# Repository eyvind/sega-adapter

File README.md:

# Sega Mega Drive (Genesis) controller to Atari 8-bit adapter

Adapt a Sega Mega Drive controller to the 9-pin Atari joystick standard
using a Microchip PIC 16F1847 microcontroller.

![An 8BitDo M30 controller above an uncased circuit board populated with
an 18-pin chip, a capacitor, a male DE-9 socket, and an IDC-connected
ribbon cable terminated by a female DE-9 plug. An 8BitDo Retro receiver
is plugged in to the adapter](img/adapter.jpeg)

This adapter is compatible with [most
computers](#computer-compatibility) that use the Atari 9-pin joystick
connector, supporting most of the features of [Sega Mega Drive
controllers](#controller-compatibility), which use the same connector
with a slightly different pinout.  The Mega Drive was known as Genesis
in the US.

Read all you need to?  [Here's how to build the adapter](#build).

## Features of this adapter

The adapter uses a microcontroller to talk to the Mega Drive controller
and map its four buttons to the three inputs available on an 8-bit
Atari.

The B button on the controller is mapped to the normal joystick button.
Buttons A and C are connected to pins 5 and 9 on the joystick port;
these can be read as extra joystick buttons by the computer.  Most games
that only support one extra button use the C button (pin 9).

### "A is Up" toggle

The start button has no natural mapping since the Atari can only read
three buttons, but a common complaint in platform games on the Atari
(and later the Amiga) was that they often used joystick Up to jump
because of the lack of extra joystick buttons.

A dedicated Up button would solve this problem, but the Start button is
not usually in a good location to be used as a jump button.  The adapter
therefore supports this feature indirectly: holding the Start button
down for a second maps the A button to Up.

Since the joystick button often starts games, a short press of the Start
button is mapped to joystick button 1.  This allows Start to both serve
its normal function (in supported games) and switch the A button between
modes.

### SNACK enhanced mode

[SNACK](https://abbuc.de/produkt/snack-adapter/) is an Atari adapter for
SNES controllers.  It has an enhanced mode that allows all of the
buttons to be read by the Atari, and this adapter supports that mode if
you have a six-button controller.

To switch to SNACK mode on a Sega controller, press Mode, Start, and C
(the right shoulder button if you're using an 8BitDo M30 controller) at
the same time.  Mode+Start+Z (left shoulder on the M30) goes back to
normal mode.

If you're using an 8BitDo Retro Receiver with an Xbox or PlayStation
controller, the button layout is different.  Press Mode+Start+X (left
shoulder) to switch to SNACK mode on these controllers, and Mode+Start+Z
(right shoulder) to go back to normal mode.

The SNES controller has four main buttons: A, B, X, and Y; left and
right shoulder buttons; and START and SELECT.

The main buttons have the same labels and approximately the same diamond
configuration as the A, B, X, and Y buttons on a Mega Drive controller,
but the AB and XY buttons are swapped.

The Mega Drive controller does not have shoulder buttons, so the Z and C
buttons are used instead.  As noted above, the 8BitDo Retro Receiver
maps Z and C to the shoulder buttons on the M30 controller.

Finally, the Mode button stands in for SELECT.

#### Notes

- SNACK mode uses the joystick ports in a completely different way to a
  normal joystick and will produce unexpected results in software that
  is not written to detect it.
- The buttons are not completely independent.  Only one of START, SELECT
  (Mode), X, and Y can be detected at any time, and any of those buttons
  will override A and B.  However, A and B are independent of each
  other, and the shoulder buttons are entirely independent.
- Centering the joystick relies on fairly precise timing to charge the
  Atari's pot capacitors to a specific range, so different computers and
  even cable lengths may make the joystick appear to be intermittently
  leaning in one direction.
- This feature is still experimental.

### Autodetection (Atari 8-bit machines only)

Because of the way the paddle circuits are used to read the second and
third button inputs, 8-bit Ataris read an unconnected second or third
button input as if the button is being held down.

This allows\* games running on the computer to detect the presence of a
multibutton controller by assuming that a button does not exist until it
has been seen to be released.  The adapter supports this autodetection
by leaving its button outputs open unless a Mega Drive controller is
detected or the corresponding button input is pulled low.

To activate the second button when a Mega Drive controller is not
connected, pin 9 on the controller input must be pulled low before the
adapter starts driving the second button output.  This means that the
second button must be pressed once before it can be detected by the
computer.

The third button output is open unless a Mega Drive controller is
detected since there is no other source for a third button input.

\* The astute reader will note that games are _required_ to ignore
button inputs until the button is released, otherwise a nonexistent
button will appear to be continually held down.

## Computer compatibility
### 8-bit Atari computers

The adapter has mostly been tested on 8-bit Ataris using
[Joy2B+](https://github.com/ascrnet/Joy2Bplus) enhanced games.

### 8-bit Commodore computers

The C64, C128, and VIC-20 can also read the second and third buttons.
The extra buttons on these machines are active high, which is opposite
to Atari and Sega.

Pulling the /C64 pin (number 4) on the PIC low inverts the outputs for
the extra buttons, allowing them to be read correctly by the 8-bit
Commodores.  The simplest way to do this is to install a jumper in the
appropriate location on the circuit board.

Because the joystick inputs of the 8-bit Commodores are somewhat
sensitive, all of the pins are normally open (floating).  The extra
button pins are pulled high when active, all other signals are pulled
low when active.

### Amiga

Unlike the 8-bit Commodores the extra buttons on the Amiga are active
low, and unlike all the 8-bit computers they are digital inputs instead
of repurposed paddle circuits.  The Atari mode supports both Atari and
Amiga by driving the pins for buttons two and three both high and low.

### Atari ST (untested)

Button two registers as the second mouse button / port 1 joystick button
if the adapter is plugged into port 0.  The ST does not support
additional joystick buttons on port 1.

## Controller compatibility
### Sega controllers

The adapter is compatible with three- and six-button Mega Drive
controllers. On six-button controllers, buttons X, Y, and Z act as
autofire versions of A, B, and C, while the Mode button is only used for
[SNACK enhanced mode](#snack-enhanced-mode).

Sega Master System controllers are theoretically supported, including
the second button, but this is untested.

### 8BitDo Retro Receiver

The adapter is extensively tested with the [8BitDo Retro Receiver for
SEGA](https://www.8bitdo.com/retro-receiver-genesis-mega-drive/).  It's
a nifty way to use wireless controllers on old hardware.

### Other joysticks or controllers

A controller or joystick with a second button that is not normally
recognised by 8-bit Atari and Commodore computers _may_ work through the
adapter.

**CAUTION:** the second button must be on pin 9 and _not_ pin 5.  Pin 5
is the power pin, and pulling it low may damage your computer or the
adapter.

Single-button joysticks will work but derive no benefit from using the
adapter.

### Atari 7800 controller, Commodore multi-button joysticks, paddles, steering wheels, etc.

These devices will not work and should not be plugged in to the adapter.

## Build

The schematics and parts list for the adapter are in the [kicad
directory](kicad).  If you don't already have a preferred way to
manufacture a PCB, you can order a set of three from [OSH
Park](https://oshpark.com/shared_projects/Nn84QTsl).  You also need a
way to [program the microcontroller](#program).

## Program

[JOY-2-PIC](https://ataribits.weebly.com/joy2pic.html) can program a PIC
using an Atari 8-bit computer's joystick port.  Boot from the .atr image
attached to each release to start programming.  If you have a USB PIC
programmer connected to a PC, use the .hex file instead.

## Modify

If you want to modify the firmware, you need the [xc8
compiler](https://www.microchipdeveloper.com/xc8:installation) from
Microchip to build it.  Run `rake` or `xc8-cc -mcpu=16f1847 -o
sega-adapter.hex *.c` to create a .hex file suitable for a PIC
programmer.

## Rationale

All right, it's time for some history.

- In 1977, Atari released the 2600 game console.
- In 1981, Commodore released the VIC-20 home computer.
- In 1984, Sega released the SG-1000 II console with one main
  improvement from the SG-1000: detachable controllers.

These machines all used the same physical connector with an almost
identical pinout for their controllers, and their manufacturers stuck
with the standard through later generations, tempting people to swap
controllers and joysticks between the systems.

Most of the time, this more or less worked.  Buttons were not always
completely compatible, but most Atari and Commodore games only supported
one button so it didn't really matter as long as one button worked.  One
important caveat: Sega chose to put power on pin 5 instead of pin 7, so
mixing and matching had the potential to cause damage to both machines
and controllers.

Initially each signal was carried by an individual pin: four pins for
directions, one for the button, two pins reserved for power and ground,
leaving two pins free for other functions.

### Mega Drive (Genesis)

For the Mega Drive, released in 1988, Sega wanted to have more buttons
(four) than there were available pins on the controller port (three).
They solved this problem by using one pin (7) as an output from the
console to the controller, allowing two pins (6 and 9) to multiplex the
A, B, C, and Start buttons.

### Joy2B+

Fast forward 20 years, to January 2019.  A poster on an [Atari 8-bit
forum](https://atariage.com/forums/topic/278884-2-button-joystick/?do=findComment&comment=4206381)
introduced a design for a three-button joystick for the 8-bit Ataris,
and -- crucially -- included patched versions of existing games that
supported the extra buttons.  This was the
[Joy2B+](https://github.com/ascrnet/Joy2Bplus) project.

Suddenly, there was a reason to connect a joystick with more than one
button to an Atari.

### 8BitDo Retro Receiver for SEGA

Finally, a month later, a Hong Kong-based company called 8BitDo released
a device that allowed Bluetooth game controllers to be used with Sega
consoles, the [8BitDo Retro Receiver for
SEGA](https://www.8bitdo.com/retro-receiver-genesis-mega-drive/)...
tantalisingly close to being compatible with Atari joystick ports.

## Pinout

```
                      PIC 16F1847
                     +---------_---------+
                     |                   |
            Atari 5 -|  1  RA2   RA1  18 |- Atari 1
                     |                   |
            Atari 6 -|  2  RA3   RA0  17 |- Atari 2
                     |                   |
            Atari 9 -|  3  RA4   RA7  16 |- Atari 3
                ___  |                   |
                C64 -|  4  RA5   RA6  15 |- Atari 4
                     |                   |
    Atari 8  SEGA 8 -|  5  GND   +5v  14 |- Atari 7  SEGA 5
                     |                   |
             SEGA 1 -|  6  RB0   RB7  13 |- SEGA 6
                     |                   |
             SEGA 2 -|  7  RB1   RB6  12 |- SEGA 7
                     |                   |
             SEGA 3 -|  8  RB2   RB5  11 |- SEGA 9
                     |                   |
             SEGA 4 -|  9  RB3   RB4  10 |- X
                     |                   |
                     +-------------------+
```

## Acknowledgements

Information on reading Sega controllers came from
https://github.com/jonthysell/SegaController/wiki/How-To-Read-Sega-Controllers
and
https://www.raspberryfield.life/2019/03/25/sega-mega-drive-genesis-6-button-xyz-controller/

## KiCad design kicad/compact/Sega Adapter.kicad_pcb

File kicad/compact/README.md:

# Compact adapter

The compact variant of the adapter is the recommended one to build.
DigiKey part numbers are provided as a convenience, but alternative
parts can certainly be used.

## BOM

| Component | DigiKey part number |
| --- | --- |
| PIC 16F1874 microcontroller | PIC16F1847-I/P-ND |
| 0.1uF capacitor | 1109PHCT-ND |
| 18-pin socket | ED3018-ND |
| D-sub male socket | A32088-ND |
| IDC header | S2011EC-05-ND |
| D-sub female plug with ribbon cable | H7FXH-0906G-ND |
| IDC connector | LKR10H-ND |
| Jumper header (optional) | S2011EC-01-ND |
| Jumper (optional) | S9001-ND |

### Optional jumper

The jumper is used to switch the adapter between Atari and C64 mode.  If
the adapter is only going to be used with one kind of computer, the
jumper and its header can either be omitted entirely (Atari/Amiga) or
replaced with a solder bridge or wire (C64/VIC-20).

### Optional joystick pigtail

Instead of using the IDC header and ribbon cable, a joystick pigtail can
be soldered directly to the board.  A cable from an old joystick or one
end of a joystick extension cable can be used for a pigtail; just make
sure that it has nine wires.

## Assembly notes

- The ribbon cable is 2m long, so it is a good idea to cut it to a more
  reasonable length.  The remaining cable can be used with standalone
  d-sub connectors (part number HHFP09H-ND) to make more adapters.

- When attaching the IDC connector to the ribbon cable, make sure that
  pin 1 (the red wire) is flush against the side and that there is a
  small gap on the other side.  This is because the connector has ten
  pins while the cable only has nine.

- Make sure that pin 1 of the cable is on the same side as pin 1 of the
  header when connecting the cable to the board.  Pin 1 is the one with
  the square pad on the circuit board.

- If you are using alternative parts, please note that there isn't much
  clearance between the IC socket and the IDC header.  Depending on the
  socket used, a shrouded IDC header may not fit.

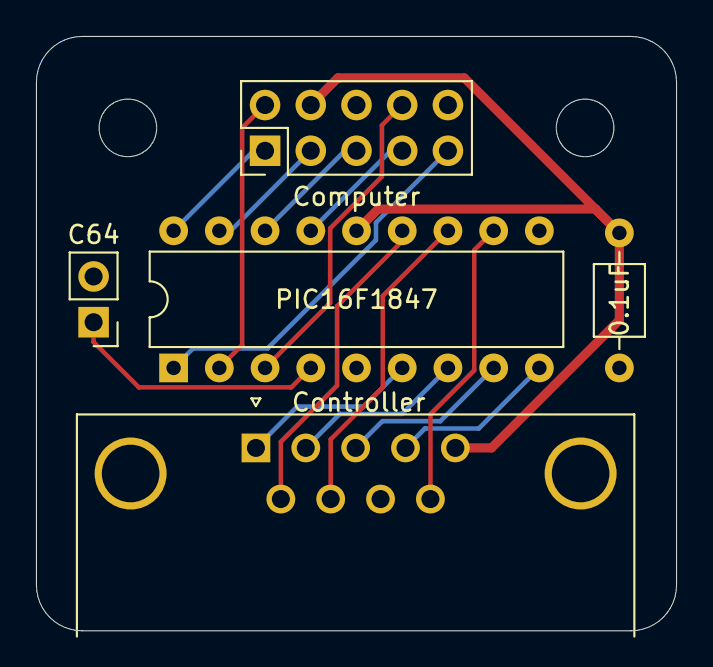
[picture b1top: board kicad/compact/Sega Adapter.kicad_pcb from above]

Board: 2 copper layers, 35.6 x 33.0 mm, 5 parts (0 on the bottom side), 17 nets.

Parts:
C1: 0.1uF; C_Axial_L3.8mm_D2.6mm_P7.50mm_Horizontal
J1: Controller; DSUB-9_Male_Horizontal_P2.77x2.84mm_EdgePinOffset7.70mm_Hou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
J2: Computer; PinHeader_2x05_P2.54mm_Vertical
JP1: C64; PinHeader_1x02_P2.54mm_Vertical
U1: PIC16F1847; DIP-18_W7.62mm

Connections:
+5V: C1.2, J1.5, J2.4, U1.14
GND: C1.1, J1.0, J1.8, J2.6, JP1.2, U1.5
unnamed: J1.1, U1.6
unnamed: J1.2, U1.7
unnamed: J1.3, U1.8
unnamed: J1.4, U1.9
unnamed: J1.6, U1.13
unnamed: J1.7, U1.12
unnamed: J1.9, U1.11
unnamed: J2.1, U1.18
unnamed: J2.2, U1.2
unnamed: J2.3, U1.17
unnamed: J2.5, U1.16
unnamed: J2.7, U1.15
unnamed: J2.8, U1.3
unnamed: J2.9, U1.1
unnamed: JP1.1, U1.4

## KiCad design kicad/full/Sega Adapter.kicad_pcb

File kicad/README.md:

# KiCad schematic

This PCB features a detachable ribbon cable to connect it to the
computer and an optional jumper to switch the adapter to C64 mode.

PCBs can be ordered in sets of three from [OSH
Park](https://oshpark.com/shared_projects/Nn84QTsl), or any other PCB
manufacturer that accepts KiCad schematics.

The previously available alternative versions of the PCB have been
removed for simplicity.  They can still be found in git history.

DigiKey part numbers are provided as a convenience but alternative
parts can certainly be used.

## BOM

| Component | DigiKey part number |
| --- | --- |
| PIC 16F1874 microcontroller | PIC16F1847-I/P-ND |
| 0.1uF capacitor | 1109PHCT-ND |
| 18-pin socket | ED3018-ND |
| D-sub male socket | A32088-ND |
| IDC header | S2011EC-05-ND |
| D-sub female plug with ribbon cable | H7FXH-0906G-ND |
| IDC connector | LKR10H-ND |
| Jumper header (optional) | S2011EC-01-ND |
| Jumper (optional) | S9001-ND |

### Optional jumper

The jumper is used to switch the adapter between Atari and C64 mode.  If
the adapter is only going to be used with one kind of computer, the
jumper and its header can either be omitted entirely (Atari/Amiga) or
replaced with a solder bridge or wire (C64/VIC-20).

### Optional joystick pigtail

Instead of using the IDC header and ribbon cable, a joystick pigtail can
be soldered directly to the board.  Any cable from an old joystick or
half of a joystick extension cable can be used for a pigtail, as long as
it has nine wires.

## Assembly notes

- The ribbon cable is 2m long, so it is a good idea to cut it to a more
  reasonable length.  The remaining cable can be used with standalone
  d-sub connectors (part number HHFP09H-ND) to make more adapters.

- When attaching the IDC connector to the ribbon cable, make sure that
  pin 1 is flush against the side and that there is a small gap on the
  other side.  This is because the connector has ten pins while the
  cable only has nine.

- Make sure that pin 1 of the cable is on the same side as pin 1 of the
  header when connecting the cable to the board.  Pin 1 is the one with
  the square pad on the circuit board.

- If you are using alternative parts, please note that there isn't much
  clearance between the IC socket and the IDC header.  Depending on the
  socket used, a shrouded IDC header may not fit.

## Licence

The schematics for this project are licensed under the [Creative Commons
Attribution 4.0
International](https://creativecommons.org/licenses/by/4.0/) licence.
See [LICENSE](LICENSE) for details.

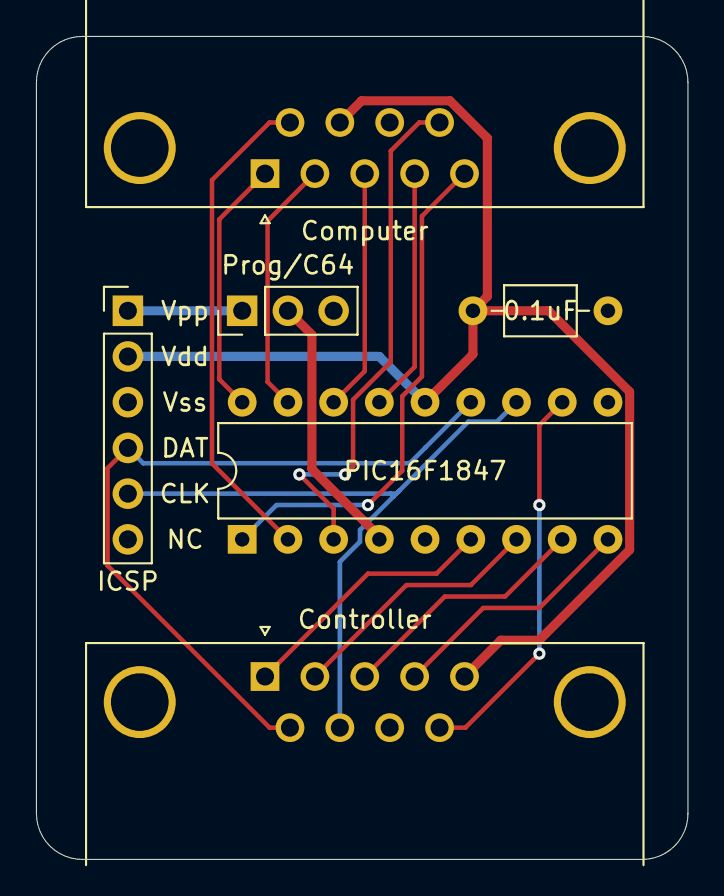
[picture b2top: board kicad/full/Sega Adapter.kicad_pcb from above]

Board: 2 copper layers, 36.2 x 45.7 mm, 6 parts (0 on the bottom side), 18 nets.

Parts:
C1: 0.1uF; C_Axial_L3.8mm_D2.6mm_P7.50mm_Horizontal
J1: Controller; DSUB-9_Male_Horizontal_P2.77x2.84mm_EdgePinOffset7.70mm_Hou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
J2: Computer; DSUB-9_Female_Horizontal_P2.77x2.84mm_EdgePinOffset7.70mm_H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
J3: ICSP; PinHeader_1x06_P2.54mm_Vertical
JP1: Prog/C64; PinHeader_1x03_P2.54mm_Vertical
U1: PIC16F1847; DIP-18_W7.62mm

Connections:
+5V: C1.2, J1.5, J2.7, J3.2, U1.14
GND: C1.1, J1.0, J1.8, J2.0, J2.8, J3.3, JP1.3, U1.5
unnamed: J1.1, U1.6
unnamed: J1.2, U1.7
unnamed: J1.3, U1.8
unnamed: J1.4, U1.9
unnamed: J1.6, J3.4, U1.13
unnamed: J1.7, J3.5, U1.12
unnamed: J1.9, U1.11
unnamed: J2.1, U1.18
unnamed: J2.2, U1.17
unnamed: J2.3, U1.16
unnamed: J2.4, U1.15
unnamed: J2.5, U1.1
unnamed: J2.6, U1.2
unnamed: J2.9, U1.3
unnamed: J3.1, JP1.1
unnamed: JP1.2, U1.4

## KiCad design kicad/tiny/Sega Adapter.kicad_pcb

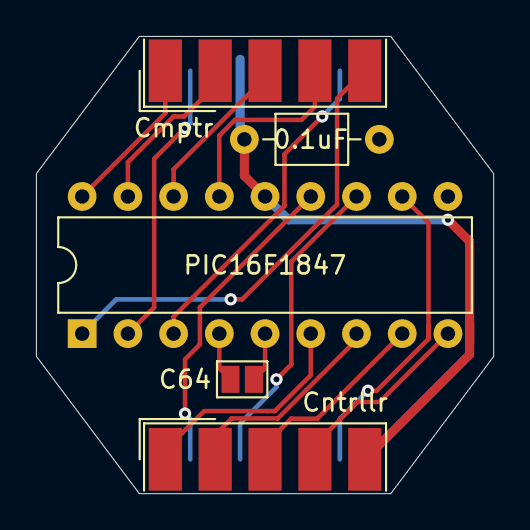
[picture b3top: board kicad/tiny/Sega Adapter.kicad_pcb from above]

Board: 2 copper layers, 25.4 x 25.4 mm, 5 parts (0 on the bottom side), 17 nets.

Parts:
C1: 0.1uF; C_Axial_L3.8mm_D2.6mm_P7.50mm_Horizontal
Cmptr: Atari; DSUB-9_Female_EdgeMount_P2.77mm
Cntrllr: Sega; DSUB-9_Male_EdgeMount_P2.77mm
JP1: C64; SolderJumper-2_P1.3mm_Open_Pad1.0x1.5mm
U1: PIC16F1847; DIP-18_W7.62mm

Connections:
+5V: C1.2, Cmptr.7, Cntrllr.5, U1.14
GND: C1.1, Cmptr.8, Cntrllr.8, JP1.2, U1.5
unnamed: Cntrllr.1, U1.6
unnamed: Cntrllr.2, U1.7
unnamed: Cntrllr.3, U1.8
unnamed: Cntrllr.4, U1.9
unnamed: Cntrllr.6, U1.13
unnamed: Cntrllr.7, U1.12
unnamed: Cntrllr.9, U1.11
unnamed: Cmptr.1, U1.18
unnamed: Cmptr.2, U1.17
unnamed: Cmptr.3, U1.16
unnamed: Cmptr.4, U1.15
unnamed: Cmptr.5, U1.1
unnamed: Cmptr.6, U1.2
unnamed: Cmptr.9, U1.3
unnamed: JP1.1, U1.4

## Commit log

2021-01-21 Correct spelling and add credit where due
    It's "Mega Drive" not "Megadrive." Apparently.
2021-01-21 Add 8-bit Commodore mode
    The second and third joystick buttons are used differently on the 8-bit
    Commodore computers; the potentiometer pins are pulled high instead of
    low when the button is pressed. Add an option to use the adapter with
    these machines.
2021-01-24 Move pins around to put outputs on PORTA
    The high-impedance input mode of the PORTB pins has insufficiently high
    impedance to use as a "low" state for buttons 2 and 3. Shift the pins
    around so that all outputs are on PORTA, where the input mode resistance
    is higher.
    Driving the pins high (for up/down/left/right/fire) or low (for buttons
    two and three) can cause problems for the 8-bit Commodores. Switching
2021-01-24 Simplify button state logic
    Make a new flag called TWO_BUTTON in the controller state to track if a
    second button is present, simplifying the code that disconnects the
    buttons in Atari mode and allowing it to use the same tristate logic as
    the Commodores.
    Remove the SIX_BUTTON flags since they're not used.
2021-01-24 Only write to TRISA once per scan
    Every write to a tristate register causes a read/modify/write cycle.
    Make a temporary variable for building the desired state, then write it
    to the register in one operation.
2021-03-07 Add Amiga support, programming info, and a wall of text
2021-04-25 Add KiCad files for pcb
2021-04-25 Add KiCad projects for two adapter variants
    The full adapter has an ICSP header for programming the PIC, a three-pin
    jumper for C64/programming mode, and through-hole D-sub connectors.
    The compact pcb removes the ICSP header but still has through-hole
    connectors and a jumper for C64 mode.
    The tiny pcb uses solder cup D-sub connectors and has a simple solder
    bridge jumper for C64 mode.
2021-05-09 Get rid of vias
2021-07-06 Switch compact adapter to IDC connector
2021-07-07 Add README and licence
    Also tweak the PCBs:
    - round the corners of the full PCB
    - add a copyright message to the full and tiny PCBs
2021-08-14 Hide the J2 label
2021-08-21 Add BOM and recommend the compact pcb
2021-08-21 Link to the schematics from the project README
2021-08-29 Add six-button support with autofire
    The select line toggle sequence to read the X, Y, Z, and MODE buttons is
    timing sensitive, and is too slow for the 8bitdo receiver with the PIC
    system clock at 500kHz (the default) or 1MHz. At 2MHz, it works.
    Without multiplexing on the computer side there's no way to use the
    extra buttons directly, but autofire is useful. Holding down X, Y, or Z
    respectively pulses the A, B, or C button at around 12Hz.
2022-08-13 Improve six-button compatibility
    Using a non-8bitdo test controller, 2MHz wasn't fast enough to enable
    six-button support. Go all the way to 32MHz (the highest clock speed on
    the 16F1847) to make it work.
2022-08-13 Save power by slowing the clock when idle
    The 32MHz clock requires 4xPLL to be enabled, but switching clocks
    resulted in the top clock speed alternating between 32MHz and 8MHz each
    cycle.
    16MHz seems to be fast enough to satisfy the test controller and does
    not require the 4xPLL.
2022-08-13 Adjust autofire
    Tune the autofire rate to match the 8BitDo adapter's native autofire,
    which is just over 16Hz. Pre-tuning, the rate was around 13Hz.
2022-08-13 Add six-button support to the README file
2022-08-13 Clarify the README a bit
2022-08-15 Add credit for six-button controller timings
2022-09-17 Add experimental SNACK support
    Hold down the MODE button to switch to SNACK mode.
    SNACK is a project that brings SNES controllers to Atari, and it has a
    "quite clever ;) but also easy to use" mapping for all SNES buttons to
    the Atari.
    The button layout is adapted to the SEGA controller thusly:
    - A and B are swapped
2022-09-19 Use SNACK buttons to switch modes
    SNACK uses START+SELECT+left/right shoulder buttons to switch between
    its classic and enhanced modes: when pressed in combination with START
    and SELECT, the right shoulder button switches to enhanced mode and the
    left goes back to classic mode.
    Since SNACK-compatible games may reference this convention, it makes
    sense to use it here.
2022-09-19 Don't toggle A-is-Up in SNACK mode
    The START key is directly useable when the controller is in SNACK mode,
    and A-is-Up is not. Don't hijack the START button when in SNACK mode.
2022-09-23 Run the SNACK cycle more often to smooth timing
    Charging the pot capacitors partway is very timing sensitive. Remove
    conditionals from the code and run a shorter charge twice as often to
    make it less jittery.
2022-09-24 Document SNACK enhanced mode
2022-12-04 Build with xc8-cc
    Building with xc8-cc instead of the older xc8 reveals some type
    warnings. Clean them up, and update the documentation and .gitignore
    for the new compiler.
2022-12-04 Refactor into more manageable source files
    Split sega-adapter.c into separate source files and add a Rakefile to
    make building easier.
2023-01-07 Add a picture of the compact adapter
2023-01-28 Add Snack support for Xbox/Playstation controllers
    The 8bitdo retro adapter's layout for Xbox/Playstation-style controllers
    needs a different Snack mapping than the Megadrive controller.
    Since the Snack adapter itself uses select/start/shoulder buttons to
    switch between enhanced and normal mode, it makes sense to use the same
    convention for this adapter:
    Start+select+
2023-01-29 Update README.md for the new SNACK mode
    The README also needed a rewrite, so give it one.
2023-01-30 Remove the full and tiny pcb variants

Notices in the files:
kicad/compact/Sega Adapter.kicad_pcb:
Copyright © 2021 Eyvind Bernhardsen
